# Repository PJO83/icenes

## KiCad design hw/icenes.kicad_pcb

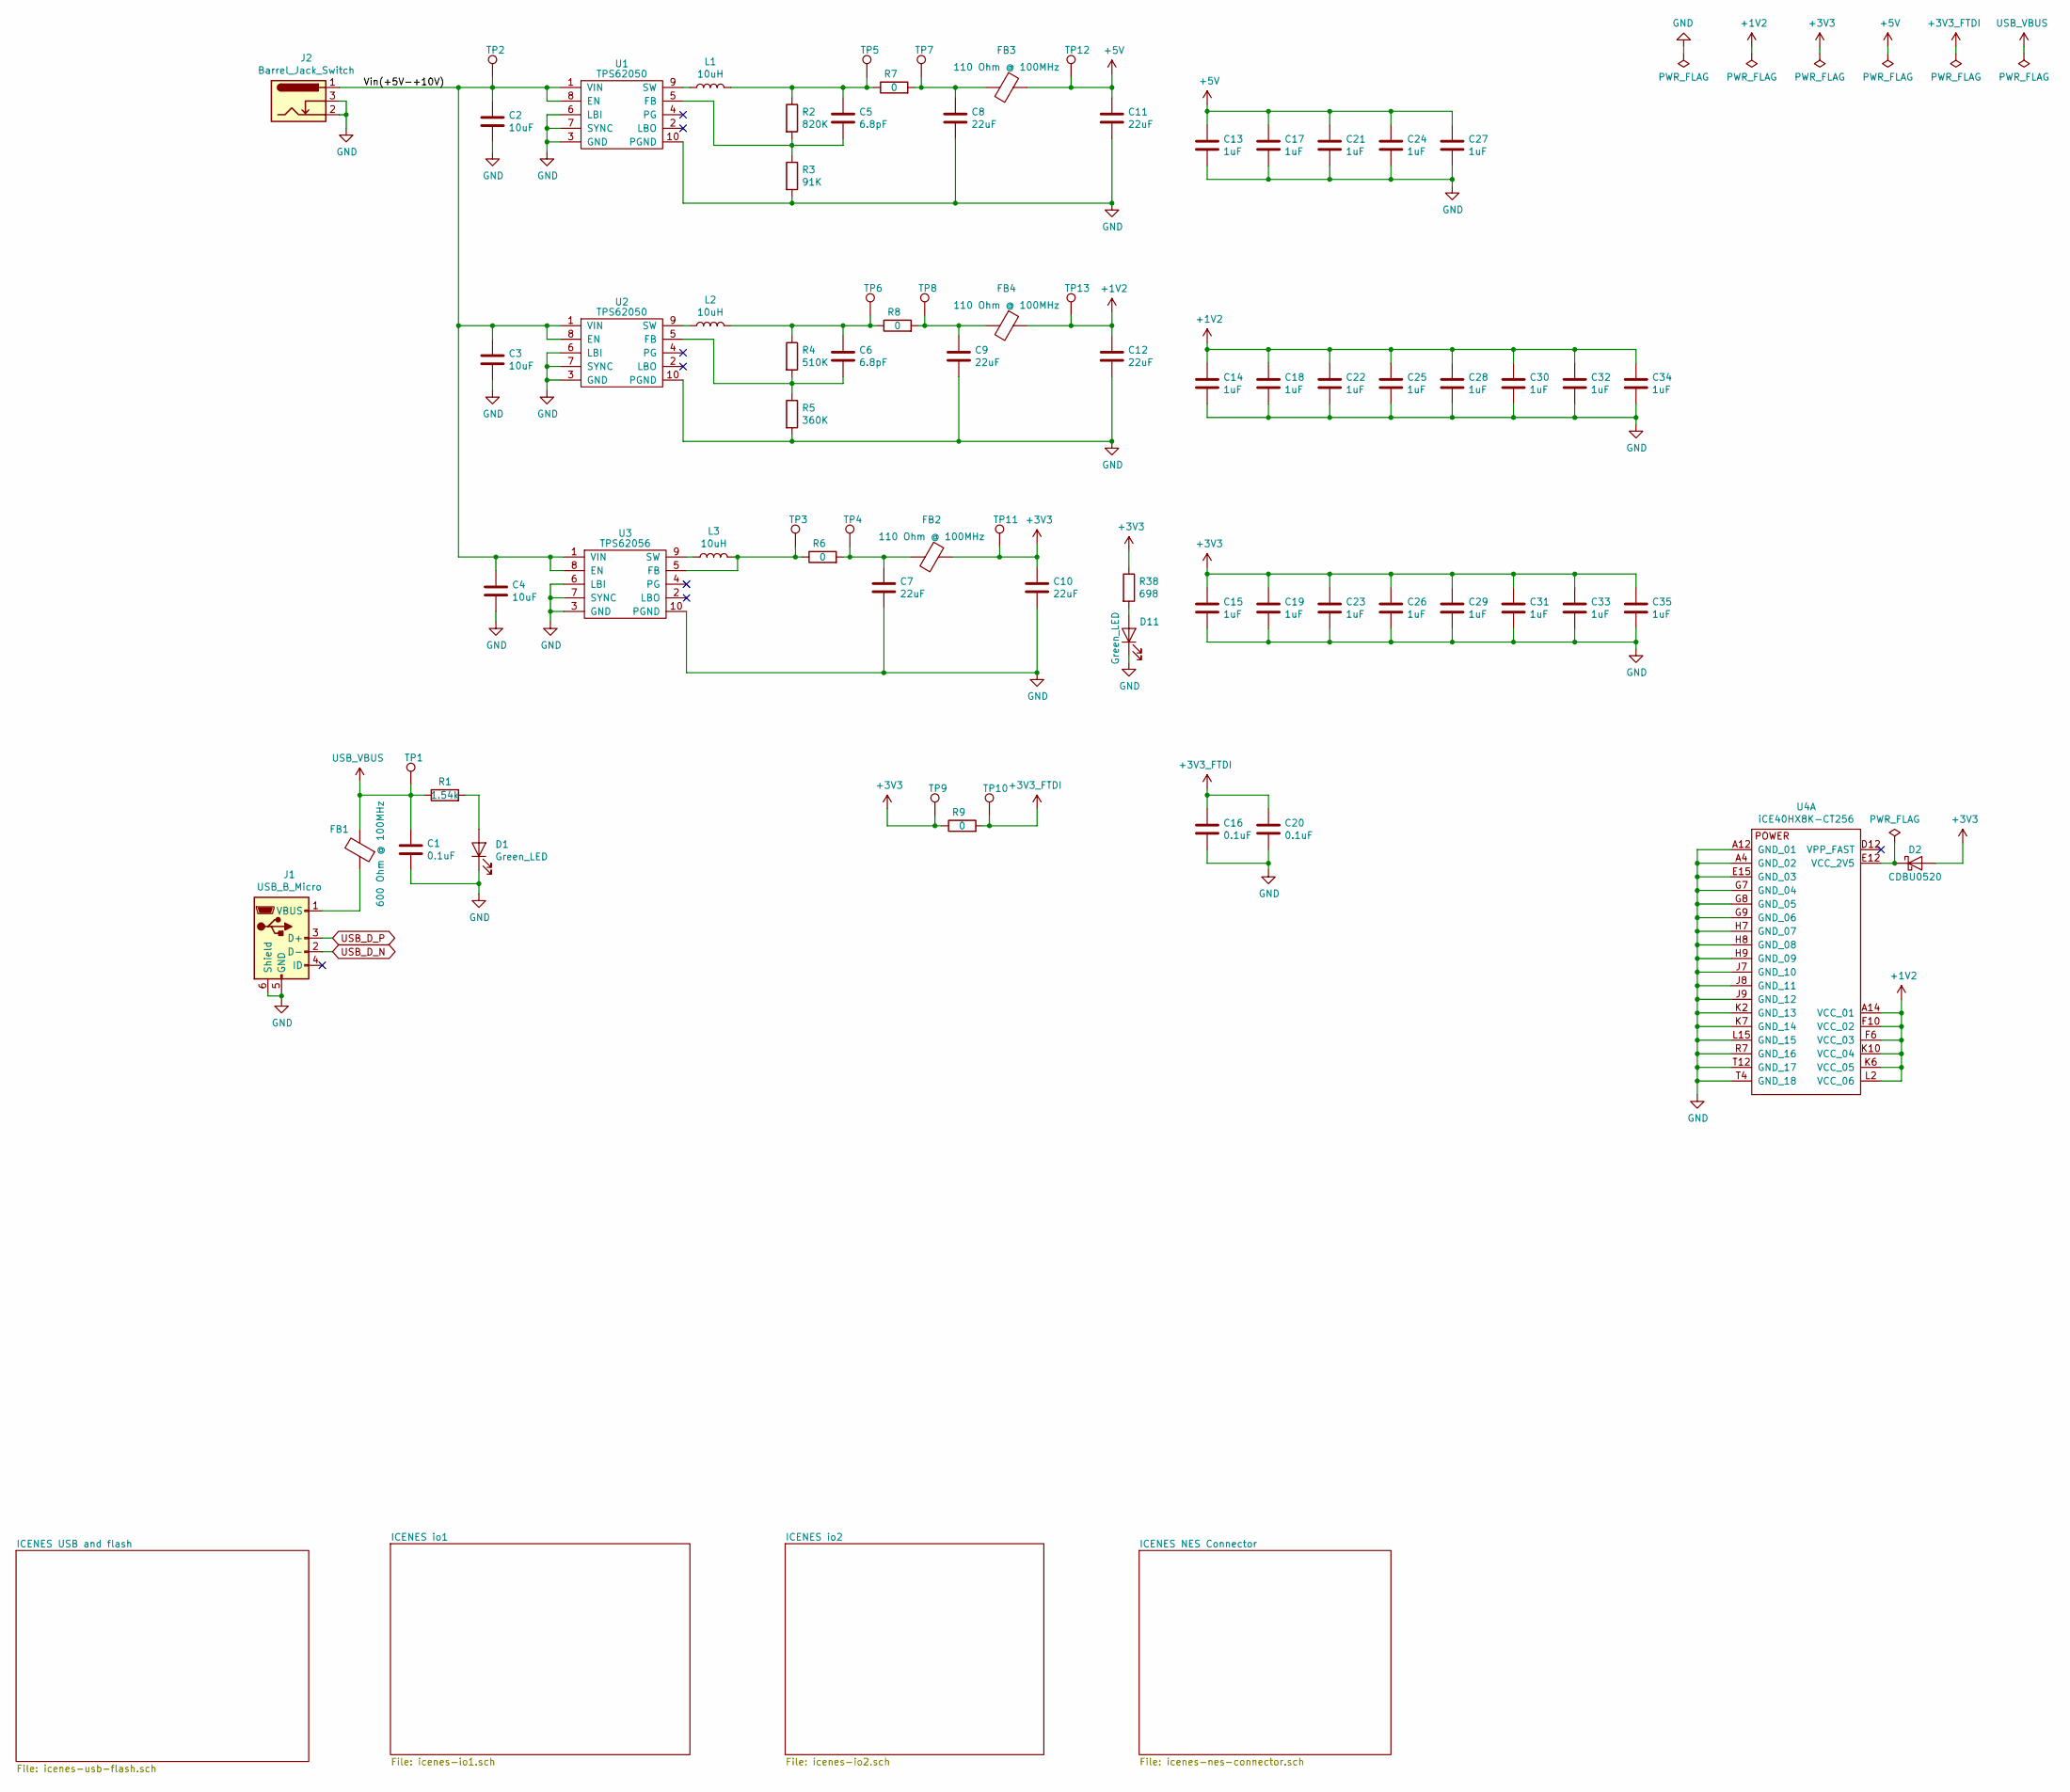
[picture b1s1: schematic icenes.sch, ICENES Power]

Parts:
C1, C16, C20: C0.1uF; C_0603_1608Metric_Pad1.05x0.95mm_HandSolder; Part number 885012206020
C2, C3, C4: C10uF; C_0603_1608Metric_Pad1.05x0.95mm_HandSolder; Part number GRM188R61A106KE69D
C5, C6: C6.8pF; C_0603_1608Metric_Pad1.05x0.95mm_HandSolder; Part number VJ0603A6R8DXQCW1BC
C7, C8, C9, C10, C11, C12: C22uF; C_0603_1608Metric_Pad1.05x0.95mm_HandSolder; Part number GRM188R61A226ME15D
C13, C14, C15, C17, C18, C19, C21, C22, C23, C24, C25, C26, C27, C28, C29, C30, C31, C32, C33, C34, C35: C1uF; C_0603_1608Metric_Pad1.05x0.95mm_HandSolder; Part number C0603C105K8PACTU
D1, D11: Green_LED; LED_0805_2012Metric_Pad1.15x1.40mm_HandSolder; Part number APTD2012LCGCK
D2: CDBU0520; D_0603_1608Metric_Pad1.05x0.95mm_HandSolder; Part number CDBU0520
FB1: FB600_500mA_0603; L_0603_1608Metric_Pad1.05x0.95mm_HandSolder; Part number KMZ1608BHR601CTDH5
FB2, FB3, FB4: FB110_4100mA_0603; L_0603_1608Metric_Pad1.05x0.95mm_HandSolder; Part number 74279228111
J1: USB_B_Micro; USB_Micro-B; Part number DX4R005JJ2R1800
J2: Barrel_Jack_Switch; BarrelJack_Horizontal; Part number 163-179PH-EX
L1, L2, L3: L10uH; Sumida_L_7.5x7.5_H4.5; Part number CDRH74NP-100MC-B
R1: R1.54k; R_0603_1608Metric_Pad1.05x0.95mm_HandSolder; Part number RC0603FR-071K54L
R2: R820K; R_0603_1608Metric_Pad1.05x0.95mm_HandSolder; Part number RC0603FR-07820KL
R3: R91K; R_0603_1608Metric_Pad1.05x0.95mm_HandSolder; Part number RC0603FR-0791KL
R4: R510K; R_0603_1608Metric_Pad1.05x0.95mm_HandSolder; Part number RC0603FR-07510KL
R5: R360K; R_0603_1608Metric_Pad1.05x0.95mm_HandSolder; Part number RC0603FR-07360KL
R6, R7, R8, R9: R0; R_0805_2012Metric_Pad1.15x1.40mm_HandSolder; Part number RC0805FR-070RL
R38: R698; R_0603_1608Metric_Pad1.05x0.95mm_HandSolder; Part number RC0603FR-07698RL
TP1, TP2, TP3, TP4, TP5, TP6, TP7, TP8, TP9, TP10, TP11, TP12, TP13: TestPoint; TestPoint_Pad_D1.0mm
U1, U2: TPS62050; VSSOP-10_3x3mm_P0.5mm; Part number TPS62050DGSR
U3: TPS62056; VSSOP-10_3x3mm_P0.5mm; Part number TPS62056DGSR
U4: iCE40HX8K-CT256; BGA-256_14.0x14.0mm_Layout16x16_P0.8mm_Ball0.45mm_Pad0.32mm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; Part number iCE40HX8K-CT256

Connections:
+1V2: C12.1, C14.1, C18.1, C22.1, C25.1, C28.1, C30.1, C32.1, C34.1, FB4.1, TP13.1, U4.A14 (VCC_01), U4.F6 (VCC_03), U4.F10 (VCC_02), U4.K6 (VCC_05), U4.K10 (VCC_04), U4.L2 (VCC_06); also elsewhere on the board
+3V3: C10.1, C15.1, C19.1, C23.1, C26.1, C29.1, C31.1, C33.1, C35.1, D2.2 (A), FB2.1, R9.1, R38.1, TP9.1, TP11.1; also elsewhere on the board
+3V3_FTDI: C16.1, C20.1, R9.2, TP10.1; also elsewhere on the board
+5V: C11.1, C13.1, C17.1, C21.1, C24.1, C27.1, FB3.1, TP12.1; also elsewhere on the board
/Vin(+5V-+10V): C2.1, C3.1, C4.1, J2.1, TP2.1, U1.1 (VIN), U1.8 (EN), U2.1 (VIN), U2.8 (EN), U3.1 (VIN), U3.8 (EN)
GND: C1.2, C2.2, C3.2, C4.2, C7.2, C8.2, C9.2, C10.2, C11.2, C12.2, C13.2, C14.2, C15.2, C16.2, C17.2, C18.2, C19.2, C20.2, C21.2, C22.2, C23.2, C24.2, C25.2, C26.2, C27.2, C28.2, C29.2, C30.2, C31.2, C32.2, C33.2, C34.2, C35.2, D1.1 (K), D11.1 (K), J1.5 (GND), J1.6 (Shield), J2.2, J2.3, R3.2, R5.2, U1.3 (GND), U1.6 (LBI), U1.7 (SYNC), U1.10 (PGND), U2.3 (GND), U2.6 (LBI), U2.7 (SYNC), U2.10 (PGND), U3.3 (GND), U3.6 (LBI), U3.7 (SYNC), U3.10 (PGND), U4.A4 (GND_02), U4.A12 (GND_01), U4.E15 (GND_03), U4.G7 (GND_04), U4.G8 (GND_05), U4.G9 (GND_06), U4.H7 (GND_07), U4.H8 (GND_08), U4.H9 (GND_09), U4.J7 (GND_10), U4.J8 (GND_11), U4.J9 (GND_12), U4.K2 (GND_13), U4.K7 (GND_14), U4.L15 (GND_15), U4.R7 (GND_16), U4.T4 (GND_18), U4.T12 (GND_17); also elsewhere on the board
unnamed: C5.1, L1.2, R2.1, R7.1, TP5.1
unnamed: C5.2, R2.2, R3.1, U1.5 (FB)
unnamed: C6.1, L2.2, R4.1, R8.1, TP6.1
unnamed: C6.2, R4.2, R5.1, U2.5 (FB)
unnamed: C7.1, FB2.2, R6.2, TP4.1
unnamed: C8.1, FB3.2, R7.2, TP7.1
unnamed: C9.1, FB4.2, R8.2, TP8.1
unnamed: D1.2 (A), R1.2
unnamed: D2.1 (K), U4.E12 (VCC_2V5)
unnamed: D11.2 (A), R38.2
unnamed: FB1.1, J1.1 (VBUS)
unnamed: L1.1, U1.9 (SW)
unnamed: L2.1, U2.9 (SW)
unnamed: L3.1, U3.9 (SW)
unnamed: L3.2, R6.1, TP3.1, U3.5 (FB)
USB_D_N: J1.2 (D-); also elsewhere on the board
USB_D_P: J1.3 (D+); also elsewhere on the board
USB_VBUS: C1.1, FB1.2, R1.1, TP1.1; also elsewhere on the board

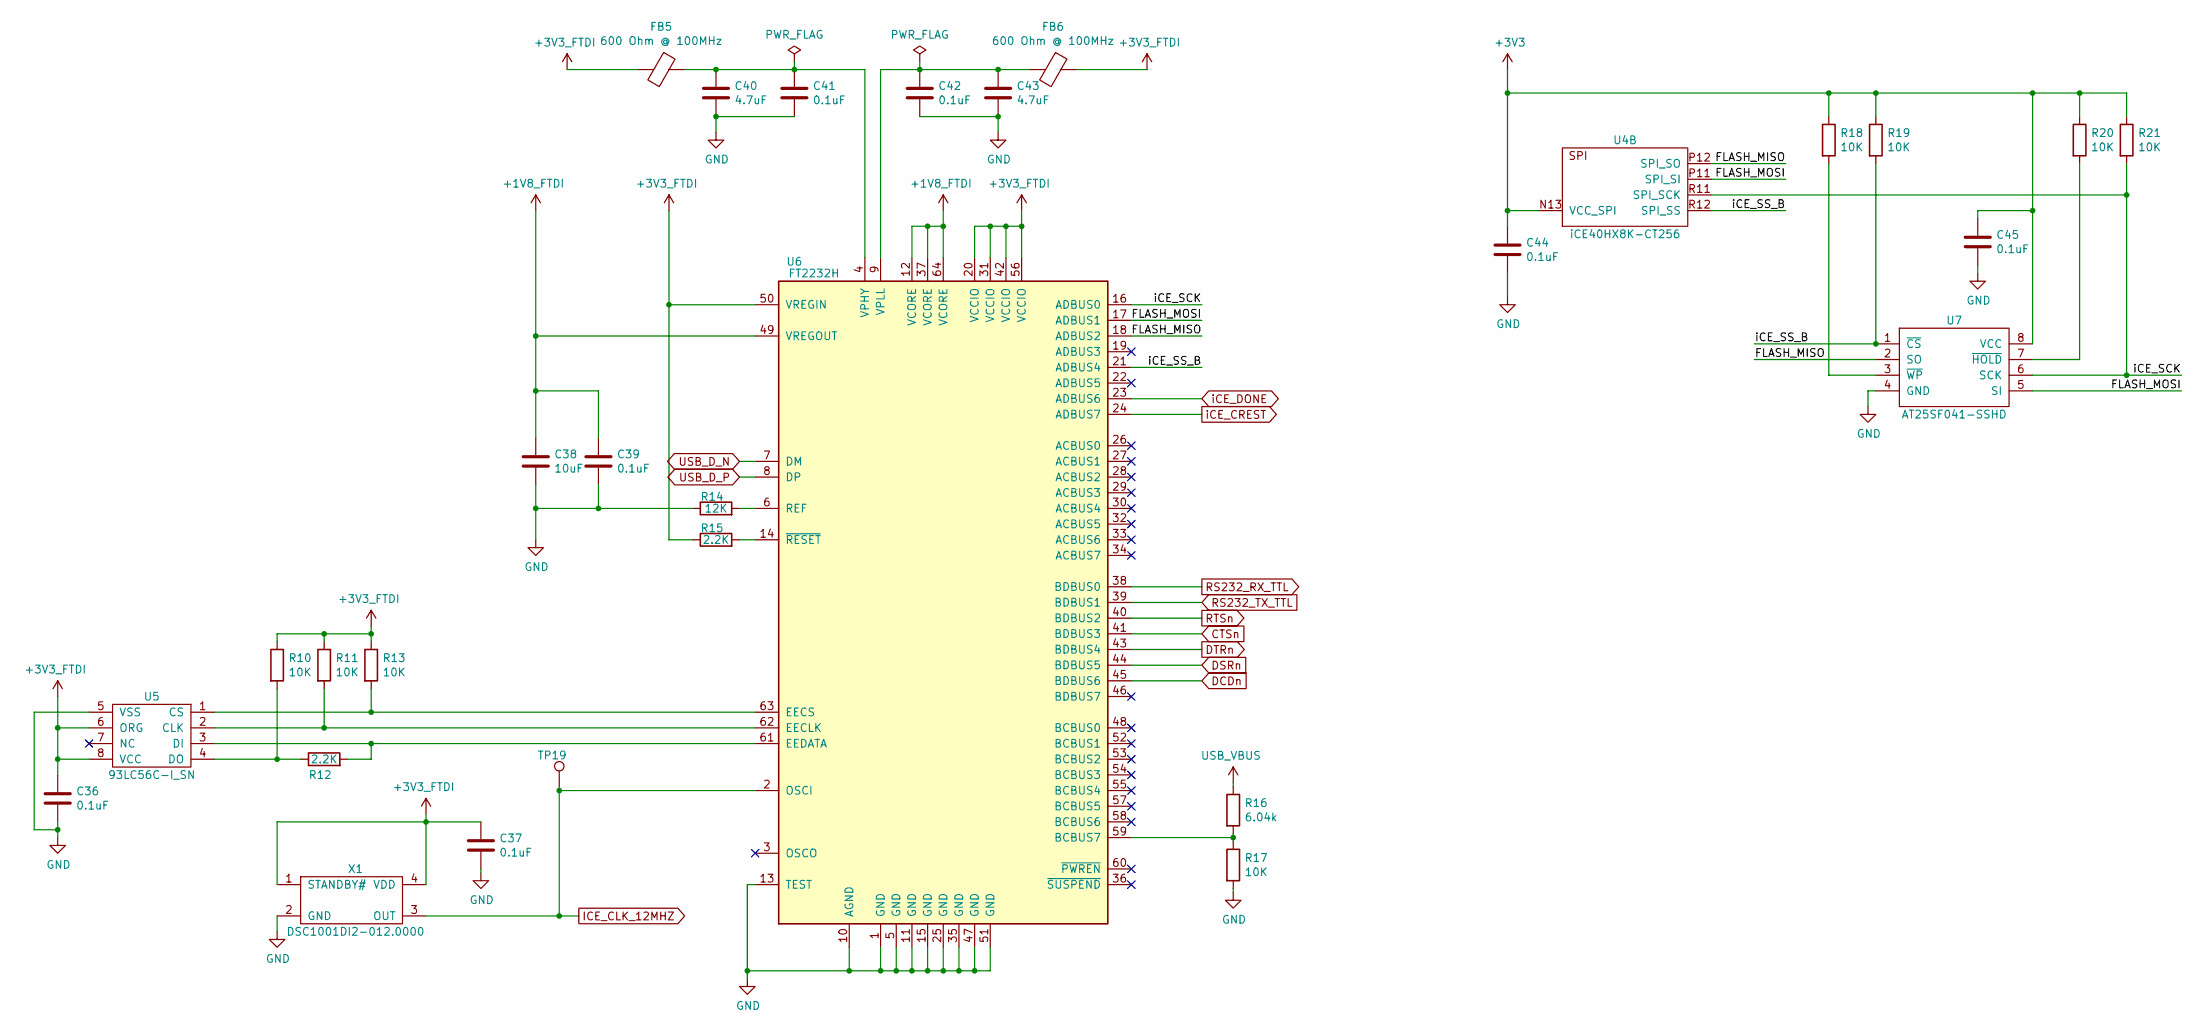
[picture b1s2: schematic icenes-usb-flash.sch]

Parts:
C36, C37, C39, C41, C42, C44, C45: C0.1uF; C_0603_1608Metric_Pad1.05x0.95mm_HandSolder; Part number 885012206020
C38: C10uF; C_0603_1608Metric_Pad1.05x0.95mm_HandSolder; Part number GRM188R61A106KE69D
C40, C43: C4.7uF; C_0603_1608Metric_Pad1.05x0.95mm_HandSolder; Part number LMK107BJ475KA-T
FB5, FB6: FB600_500mA_0603; L_0603_1608Metric_Pad1.05x0.95mm_HandSolder; Part number KMZ1608BHR601CTDH5
R10, R11, R13, R17, R18, R19, R20, R21: R10K; R_0603_1608Metric_Pad1.05x0.95mm_HandSolder; Part number RC0603FR-0710KL
R12, R15: R2.2K; R_0603_1608Metric_Pad1.05x0.95mm_HandSolder; Part number RC0603FR-072K2L
R14: R12K; R_0603_1608Metric_Pad1.05x0.95mm_HandSolder; Part number RC0603FR-0712KL
R16: R6.04k; R_0603_1608Metric_Pad1.05x0.95mm_HandSolder; Part number RC0603FR-076K04L
TP19: TestPoint; TestPoint_Pad_D1.0mm
U4: iCE40HX8K-CT256; BGA-256_14.0x14.0mm_Layout16x16_P0.8mm_Ball0.45mm_Pad0.32mm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; Part number iCE40HX8K-CT256
U5: 93LC56C-I_SN; SOIC-8_3.9x4.9mm_P1.27mm; Part number 93LC56C-I/SN
U6: FT2232H; LQFP-64_10x10mm_P0.5mm; Part number FT2232HL
U7: AT25SF041-SSHD; SOIC-8_3.9x4.9mm_P1.27mm; Part number AT25SF041-SSHD-B
X1: DSC1001DI2-012.0000; MEMS_Microship_Ocillator_SMD_CDFN-4_2.5x2.0mm; Part number DSC1001DI2-012.0000T

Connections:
+1V8_FTDI: C38.1, C39.1, U6.12 (VCORE), U6.37 (VCORE), U6.49 (VREGOUT), U6.64 (VCORE)
+3V3: C44.1, C45.1, R18.1, R19.1, R20.1, R21.1, U4.N13 (VCC_SPI), U7.8 (VCC); also elsewhere on the board
+3V3_FTDI: C36.1, C37.1, FB5.2, FB6.1, R10.1, R11.1, R13.1, R15.1, U5.6 (ORG), U5.8 (VCC), U6.20 (VCCIO), U6.31 (VCCIO), U6.42 (VCCIO), U6.50 (VREGIN), U6.56 (VCCIO), X1.1 (STANDBY#), X1.4 (VDD); also elsewhere on the board
/ICENES USB and flash/FLASH_MISO: U4.P12 (SPI_SO), U6.18 (ADBUS2), U7.2 (SO)
/ICENES USB and flash/FLASH_MOSI: U4.P11 (SPI_SI), U6.17 (ADBUS1), U7.5 (SI)
/ICENES USB and flash/iCE_SCK: R21.2, U4.R11 (SPI_SCK), U6.16 (ADBUS0), U7.6 (SCK)
/ICENES USB and flash/iCE_SS_B: R19.2, U4.R12 (SPI_SS), U6.21 (ADBUS4), U7.1 (~CS)
CTSn: U6.41 (BDBUS3); also elsewhere on the board
DCDn: U6.45 (BDBUS6); also elsewhere on the board
DSRn: U6.44 (BDBUS5); also elsewhere on the board
DTRn: U6.43 (BDBUS4); also elsewhere on the board
GND: C36.2, C37.2, C38.2, C39.2, C40.2, C41.2, C42.2, C43.2, C44.2, C45.2, R14.1, R17.2, U5.5 (VSS), U6.1 (GND), U6.5 (GND), U6.10 (AGND), U6.11 (GND), U6.13 (TEST), U6.15 (GND), U6.25 (GND), U6.35 (GND), U6.47 (GND), U6.51 (GND), U7.4 (GND), X1.2 (GND); also elsewhere on the board
ICE_CLK_12MHZ: TP19.1, U6.2 (OSCI), X1.3 (OUT); also elsewhere on the board
unnamed: C40.1, C41.1, FB5.1, U6.4 (VPHY)
unnamed: C42.1, C43.1, FB6.2, U6.9 (VPLL)
unnamed: R10.2, R12.1, U5.4 (DO)
unnamed: R11.2, U5.2 (CLK), U6.62 (EECLK)
unnamed: R12.2, U5.3 (DI), U6.61 (EEDATA)
unnamed: R13.2, U5.1 (CS), U6.63 (EECS)
unnamed: R14.2, U6.6 (REF)
unnamed: R15.2, U6.14 (~RESET)
unnamed: R16.2, R17.1, U6.59 (BCBUS7)
unnamed: R18.2, U7.3 (~WP)
unnamed: R20.2, U7.7 (~HOLD)
RS232_RX_TTL: U6.38 (BDBUS0); also elsewhere on the board
RS232_TX_TTL: U6.39 (BDBUS1); also elsewhere on the board
RTSn: U6.40 (BDBUS2); also elsewhere on the board
USB_D_N: U6.7 (DM); also elsewhere on the board
USB_D_P: U6.8 (DP); also elsewhere on the board
USB_VBUS: R16.1; also elsewhere on the board
iCE_CREST: U6.24 (ADBUS7); also elsewhere on the board
iCE_DONE: U6.23 (ADBUS6); also elsewhere on the board

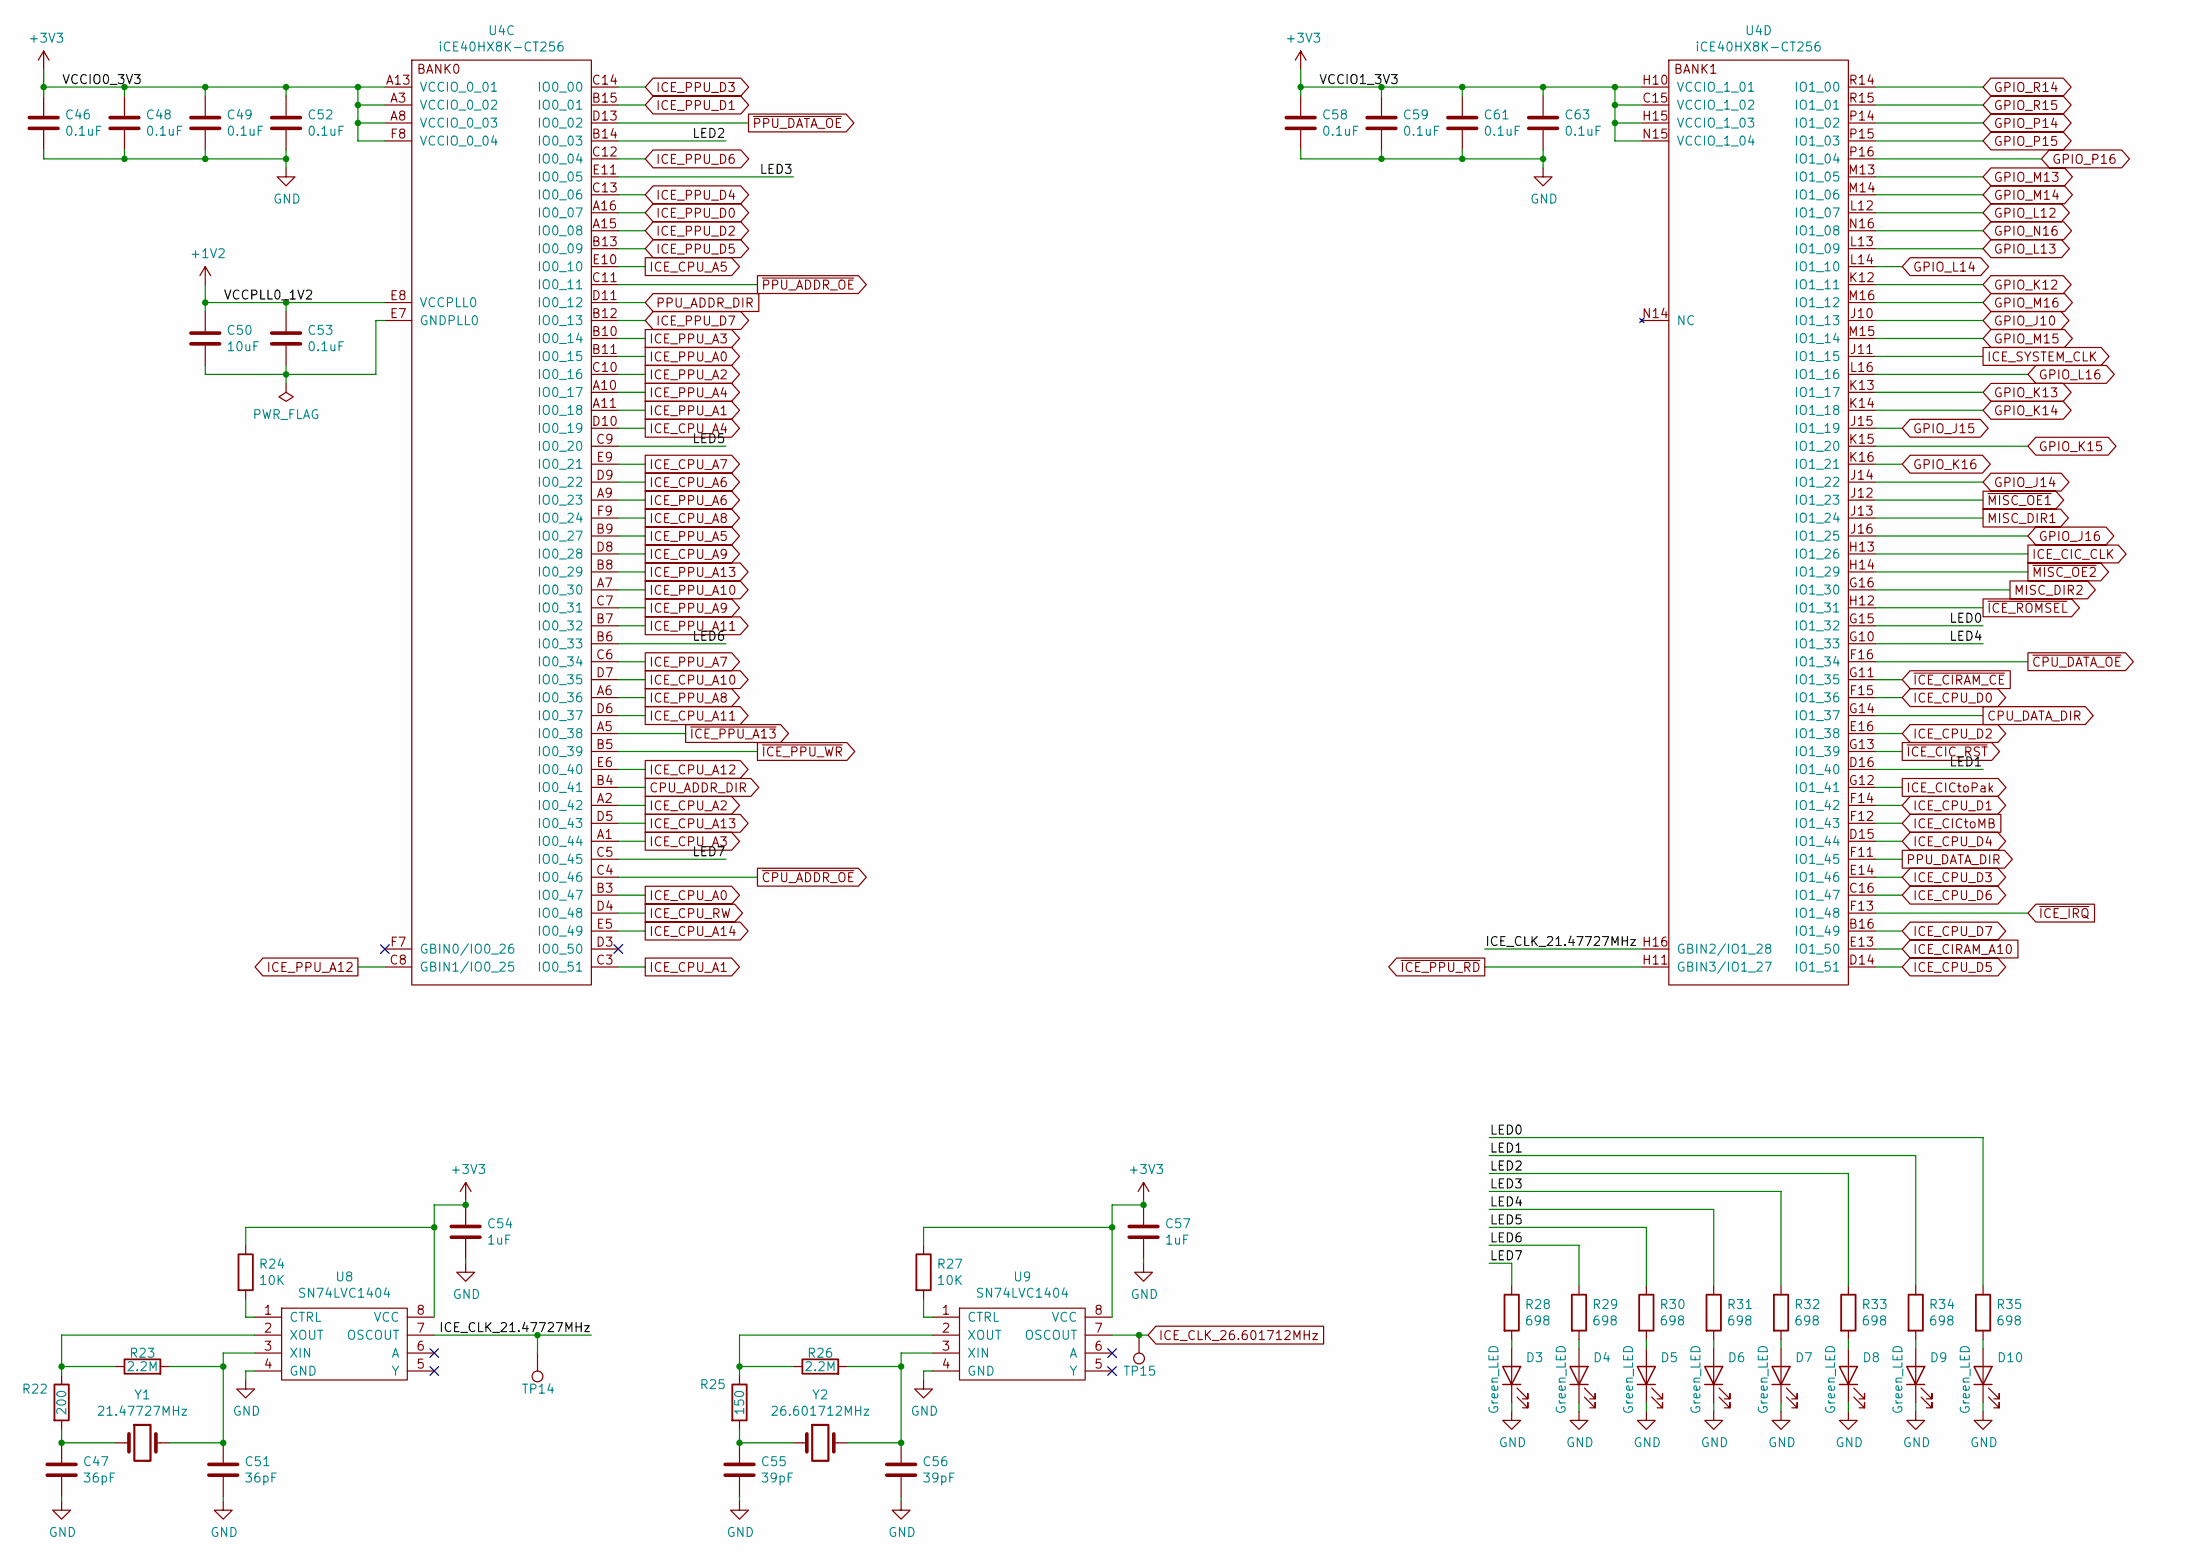
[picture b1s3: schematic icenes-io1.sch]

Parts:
C46, C48, C49, C52, C53, C58, C59, C61, C63: C0.1uF; C_0603_1608Metric_Pad1.05x0.95mm_HandSolder; Part number 885012206020
C47, C51: C36pF; C_0603_1608Metric_Pad1.05x0.95mm_HandSolder; Part number CC0603FRNPO9BN360
C50: C10uF; C_0603_1608Metric_Pad1.05x0.95mm_HandSolder; Part number GRM188R61A106KE69D
C54, C57: C1uF; C_0603_1608Metric_Pad1.05x0.95mm_HandSolder; Part number C0603C105K8PACTU
C55, C56: C39pF; C_0603_1608Metric_Pad1.05x0.95mm_HandSolder; Part number CC0603FRNPO9BN390
D3, D4, D5, D6, D7, D8, D9, D10: Green_LED; LED_0805_2012Metric_Pad1.15x1.40mm_HandSolder; Part number APTD2012LCGCK
R22: R200; R_0603_1608Metric_Pad1.05x0.95mm_HandSolder; Part number RC0603FR-07200RL
R23, R26: R2.2M; R_0603_1608Metric_Pad1.05x0.95mm_HandSolder; Part number RC0603FR-072M2L
R24, R27: R10K; R_0603_1608Metric_Pad1.05x0.95mm_HandSolder; Part number RC0603FR-0710KL
R25: R150; R_0603_1608Metric_Pad1.05x0.95mm_HandSolder; Part number RC0603FR-07150RL
R28, R29, R30, R31, R32, R33, R34, R35: R698; R_0603_1608Metric_Pad1.05x0.95mm_HandSolder; Part number RC0603FR-07698RL
TP14, TP15: TestPoint; TestPoint_Pad_D1.0mm
U4: iCE40HX8K-CT256; BGA-256_14.0x14.0mm_Layout16x16_P0.8mm_Ball0.45mm_Pad0.32mm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; Part number iCE40HX8K-CT256
U8, U9: SN74LVC1404; VSSOP-8_2.3x2mm_P0.5mm; Part number SN74LVC1404DCUR
Y1: 21.47727MHz; Crystal_HC49-4H_Vertical; Part number HC-49/U-S21477270ABJB
Y2: 26.601712MHz; Crystal_HC49-4H_Vertical; Part number ?

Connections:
+1V2: C50.1, C53.1, U4.E8 (VCCPLL0); also elsewhere on the board
+3V3: C46.1, C48.1, C49.1, C52.1, C54.1, C57.1, C58.1, C59.1, C61.1, C63.1, R24.1, R27.1, U4.A3 (VCCIO_0_02), U4.A8 (VCCIO_0_03), U4.A13 (VCCIO_0_01), U4.C15 (VCCIO_1_02), U4.F8 (VCCIO_0_04), U4.H10 (VCCIO_1_01), U4.H15 (VCCIO_1_03), U4.N15 (VCCIO_1_04), U8.8 (VCC), U9.8 (VCC); also elsewhere on the board
/ICENES io1/ICE_CLK_21.47727MHz: TP14.1, U4.H16 (GBIN2/IO1_28), U8.7 (OSCOUT)
/ICENES io1/LED0: R35.1, U4.G15 (IO1_32)
/ICENES io1/LED1: R34.1, U4.D16 (IO1_40)
/ICENES io1/LED2: R33.1, U4.B14 (IO0_03)
/ICENES io1/LED3: R32.1, U4.E11 (IO0_05)
/ICENES io1/LED4: R31.1, U4.G10 (IO1_33)
/ICENES io1/LED5: R30.1, U4.C9 (IO0_20)
/ICENES io1/LED6: R29.1, U4.B6 (IO0_33)
/ICENES io1/LED7: R28.1, U4.C5 (IO0_45)
CPU_ADDR_DIR: U4.B4 (IO0_41); also elsewhere on the board
CPU_DATA_DIR: U4.G14 (IO1_37); also elsewhere on the board
GND: C46.2, C47.2, C48.2, C49.2, C51.2, C52.2, C54.2, C55.2, C56.2, C57.2, C58.2, C59.2, C61.2, C63.2, D3.1 (K), D4.1 (K), D5.1 (K), D6.1 (K), D7.1 (K), D8.1 (K), D9.1 (K), D10.1 (K), U8.4 (GND), U9.4 (GND); also elsewhere on the board
GPIO_J10: U4.J10 (IO1_13); also elsewhere on the board
GPIO_J14: U4.J14 (IO1_22); also elsewhere on the board
GPIO_J15: U4.J15 (IO1_19); also elsewhere on the board
GPIO_J16: U4.J16 (IO1_25); also elsewhere on the board
GPIO_K12: U4.K12 (IO1_11); also elsewhere on the board
GPIO_K13: U4.K13 (IO1_17); also elsewhere on the board
GPIO_K14: U4.K14 (IO1_18); also elsewhere on the board
GPIO_K15: U4.K15 (IO1_20); also elsewhere on the board
GPIO_K16: U4.K16 (IO1_21); also elsewhere on the board
GPIO_L12: U4.L12 (IO1_07); also elsewhere on the board
GPIO_L13: U4.L13 (IO1_09); also elsewhere on the board
GPIO_L14: U4.L14 (IO1_10); also elsewhere on the board
GPIO_L16: U4.L16 (IO1_16); also elsewhere on the board
GPIO_M13: U4.M13 (IO1_05); also elsewhere on the board
GPIO_M14: U4.M14 (IO1_06); also elsewhere on the board
GPIO_M15: U4.M15 (IO1_14); also elsewhere on the board
GPIO_M16: U4.M16 (IO1_12); also elsewhere on the board
GPIO_N16: U4.N16 (IO1_08); also elsewhere on the board
GPIO_P14: U4.P14 (IO1_02); also elsewhere on the board
GPIO_P15: U4.P15 (IO1_03); also elsewhere on the board
GPIO_P16: U4.P16 (IO1_04); also elsewhere on the board
GPIO_R14: U4.R14 (IO1_00); also elsewhere on the board
GPIO_R15: U4.R15 (IO1_01); also elsewhere on the board
ICE_CIC_CLK: U4.H13 (IO1_26); also elsewhere on the board
ICE_CICtoMB: U4.F12 (IO1_43); also elsewhere on the board
ICE_CICtoPak: U4.G12 (IO1_41); also elsewhere on the board
ICE_CIRAM_A10: U4.E13 (IO1_50); also elsewhere on the board
ICE_CLK_26.601712MHz: TP15.1, U9.7 (OSCOUT); also elsewhere on the board
ICE_CPU_A0: U4.B3 (IO0_47); also elsewhere on the board
ICE_CPU_A1: U4.C3 (IO0_51); also elsewhere on the board
ICE_CPU_A2: U4.A2 (IO0_42); also elsewhere on the board
ICE_CPU_A3: U4.A1 (IO0_44); also elsewhere on the board
ICE_CPU_A4: U4.D10 (IO0_19); also elsewhere on the board
ICE_CPU_A5: U4.E10 (IO0_10); also elsewhere on the board
ICE_CPU_A6: U4.D9 (IO0_22); also elsewhere on the board
ICE_CPU_A7: U4.E9 (IO0_21); also elsewhere on the board
ICE_CPU_A8: U4.F9 (IO0_24); also elsewhere on the board
ICE_CPU_A9: U4.D8 (IO0_28); also elsewhere on the board
ICE_CPU_A10: U4.D7 (IO0_35); also elsewhere on the board
ICE_CPU_A11: U4.D6 (IO0_37); also elsewhere on the board
ICE_CPU_A12: U4.E6 (IO0_40); also elsewhere on the board
ICE_CPU_A13: U4.D5 (IO0_43); also elsewhere on the board
ICE_CPU_A14: U4.E5 (IO0_49); also elsewhere on the board
ICE_CPU_D0: U4.F15 (IO1_36); also elsewhere on the board
ICE_CPU_D1: U4.F14 (IO1_42); also elsewhere on the board
ICE_CPU_D2: U4.E16 (IO1_38); also elsewhere on the board
ICE_CPU_D3: U4.E14 (IO1_46); also elsewhere on the board
ICE_CPU_D4: U4.D15 (IO1_44); also elsewhere on the board
ICE_CPU_D5: U4.D14 (IO1_51); also elsewhere on the board
ICE_CPU_D6: U4.C16 (IO1_47); also elsewhere on the board
ICE_CPU_D7: U4.B16 (IO1_49); also elsewhere on the board
ICE_CPU_RW: U4.D4 (IO0_48); also elsewhere on the board
ICE_PPU_A0: U4.B11 (IO0_15); also elsewhere on the board
ICE_PPU_A1: U4.A11 (IO0_18); also elsewhere on the board
ICE_PPU_A2: U4.C10 (IO0_16); also elsewhere on the board
ICE_PPU_A3: U4.B10 (IO0_14); also elsewhere on the board
ICE_PPU_A4: U4.A10 (IO0_17); also elsewhere on the board
ICE_PPU_A5: U4.B9 (IO0_27); also elsewhere on the board
ICE_PPU_A6: U4.A9 (IO0_23); also elsewhere on the board
ICE_PPU_A7: U4.C6 (IO0_34); also elsewhere on the board
ICE_PPU_A8: U4.A6 (IO0_36); also elsewhere on the board
ICE_PPU_A9: U4.C7 (IO0_31); also elsewhere on the board
ICE_PPU_A10: U4.A7 (IO0_30); also elsewhere on the board
ICE_PPU_A11: U4.B7 (IO0_32); also elsewhere on the board
ICE_PPU_A12: U4.C8 (GBIN1/IO0_25); also elsewhere on the board
ICE_PPU_A13: U4.B8 (IO0_29); also elsewhere on the board
ICE_PPU_D0: U4.A16 (IO0_07); also elsewhere on the board
ICE_PPU_D1: U4.B15 (IO0_01); also elsewhere on the board
ICE_PPU_D2: U4.A15 (IO0_08); also elsewhere on the board
ICE_PPU_D3: U4.C14 (IO0_00); also elsewhere on the board
ICE_PPU_D4: U4.C13 (IO0_06); also elsewhere on the board
ICE_PPU_D5: U4.B13 (IO0_09); also elsewhere on the board
ICE_PPU_D6: U4.C12 (IO0_04); also elsewhere on the board
ICE_PPU_D7: U4.B12 (IO0_13); also elsewhere on the board
ICE_SYSTEM_CLK: U4.J11 (IO1_15); also elsewhere on the board
MISC_DIR1: U4.J13 (IO1_24); also elsewhere on the board
MISC_DIR2: U4.G16 (IO1_30); also elsewhere on the board
unnamed: C47.1, R22.2, Y1.1
unnamed: C50.2, C53.2, U4.E7 (GNDPLL0)
unnamed: C51.1, R23.2, U8.3 (XIN), Y1.2
unnamed: C55.1, R25.2, Y2.1
unnamed: C56.1, R26.2, U9.3 (XIN), Y2.2
unnamed: D3.2 (A), R28.2
unnamed: D4.2 (A), R29.2
unnamed: D5.2 (A), R30.2
unnamed: D6.2 (A), R31.2
unnamed: D7.2 (A), R32.2
unnamed: D8.2 (A), R33.2
unnamed: D9.2 (A), R34.2
unnamed: D10.2 (A), R35.2
unnamed: R22.1, R23.1, U8.2 (XOUT)
unnamed: R24.2, U8.1 (CTRL)
unnamed: R25.1, R26.1, U9.2 (XOUT)
unnamed: R27.2, U9.1 (CTRL)
PPU_ADDR_DIR: U4.D11 (IO0_12); also elsewhere on the board
PPU_DATA_DIR: U4.F11 (IO1_45); also elsewhere on the board
~CPU_ADDR_OE: U4.C4 (IO0_46); also elsewhere on the board
~CPU_DATA_OE: U4.F16 (IO1_34); also elsewhere on the board
~ICE_CIC_RST: U4.G13 (IO1_39); also elsewhere on the board
~ICE_CIRAM_CE: U4.G11 (IO1_35); also elsewhere on the board
~ICE_IRQ: U4.F13 (IO1_48); also elsewhere on the board
~ICE_PPU_A13: U4.A5 (IO0_38); also elsewhere on the board
~ICE_PPU_RD: U4.H11 (GBIN3/IO1_27); also elsewhere on the board
~ICE_PPU_WR: U4.B5 (IO0_39); also elsewhere on the board
~ICE_ROMSEL: U4.H12 (IO1_31); also elsewhere on the board
~MISC_OE1: U4.J12 (IO1_23); also elsewhere on the board
~MISC_OE2: U4.H14 (IO1_29); also elsewhere on the board
~PPU_ADDR_OE: U4.C11 (IO0_11); also elsewhere on the board
~PPU_DATA_OE: U4.D13 (IO0_02); also elsewhere on the board
